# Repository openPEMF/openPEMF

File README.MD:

# <openPEMF>

## Description

Open source PEMF project that includes the hardware and firmware for anyone looking to build their own PEMF device

- Aren't there already some open source PEMF projects?  
    Yes, but many of them do not create the same fields used in the majority of published PEMF parameters. Most of them also have switching characteristics that cause spurious spike and oscillations that could be considered "dirty electricity"

- Why share this project?  
    Because PEMF with the right parameters has the ability to change peoples lives. From regenerating cartilage to reducing inflammation, many people get out of pain they have had for years. Something this powerful should not be stuck behind high price tags.

- What problem does it solve?  
    PEMF devices with good parameters cost a lot, cheap PEMF devices do not create magnetic fields that use the parameters used in the majority of PEMF studies

This open source PEMF project provides all the files necessary to make your own PEMF device that can be used to re-create the majority of PEMF parameters used in the majority of published PEMF studies.

PEMF has been proven to do lots of amazing things including regenerate cartilage and decrease inflammation, but don't take our word for it, go read some of the published studies and take a look at the science yourself!

The project allows you to tune your own magnetic field intensity and slew rate. This can be accomplished by either changing the voltage from the power supply, or by changing the pulse width.

Reach out with any questions or suggestions! Lets build this together and create a future where all people can access PEMF and benefit from the improved quality of life!
You can reach us at openpemf@gmail.com

## Table of Contents

- [How To Build](#How-to-build)
- [Usage](#usage)
- [Features](#features)

## How to build

The Gerber files, BOM and .POS files are already for purchase at JLCPCB.com. You should be able to upload these to JLCPCB and order complete (or mostly complete - depending on part availability) PCBs ready to run!

Once you have your PCBs, the first thing that you will want to do is upload the arduino code. The file "TEST.ino" is set up to run at 10hz and if you don't want to make any changes you can simply upload this file using the Arduino IDE. You will need to install the Raspberry Pi Pico board definitions since this design uses an RP2040 as it's processor. If you want to re-upload code, there are 2 holes in the pcb that you can bridge with a paperclip to get it into bootloader mode.

If you are not familiar with arduino or PCB ordering we can send out a kit. Email us at openpemf@gmail.com.

This board is designed to fit in this enclosure:
https://www.ebay.com/itm/266629727778?mkcid=16&mkevt=1&mkrid=711-127632-2357-0&ssspo=g7l9ZZJUQN-&sssrc=2047675&ssuid=7-kgmmceqts&widget_ver=artemis&media=COPY

You can see that we used a simple circular connector to get the PEMF power through the enclosure. Ideally a 4 pin connector would be used for larger coils/currents. A handheld drill is an okay option to add the holes. Another option would be something 3D printed or laser cut. Please contribute these if you end up making them!

The coil should be wound from some form of wire. The closer the wires are together, the more efficient the coil will be. Using regular insulated wire still works well, but you will get more magnetic field from using enameled magnet wire.

Here is what our prototype coil looked like:

This sensor is great to see what the fields look like around your coil. Simply give it power and connect it to an oscilloscope:
https://www.digikey.com/en/products/detail/asahi-kasei-microdevices-akm/EQ733L/5822654

The coil we made had around 3 mT at the center, and around 10 mT close to the wires.

You will want a power supply that can run the board well. We found that this one worked well:
https://www.digikey.com/en/products/detail/fsp-technology-inc/FSP040-DWAN3/15713237 

## Usage
Simply place the loop over any part of your body that needs improvement. We like to look up published studies to see how long to use the PEMF for. You can even wind coils that are smaller with higher intensity or larger for a larger magnetic field.

## Features

There are a lot of features to OpenPEMF! Here are a few:
* Mosfet gate slew is limited -  this prevents parasitic turn on during the falling side of the signal
* There is an RC snubber across the h-bridge, removing certain oscillations that are not wanted
* Bi-polar pulses
* Programmable frequencies

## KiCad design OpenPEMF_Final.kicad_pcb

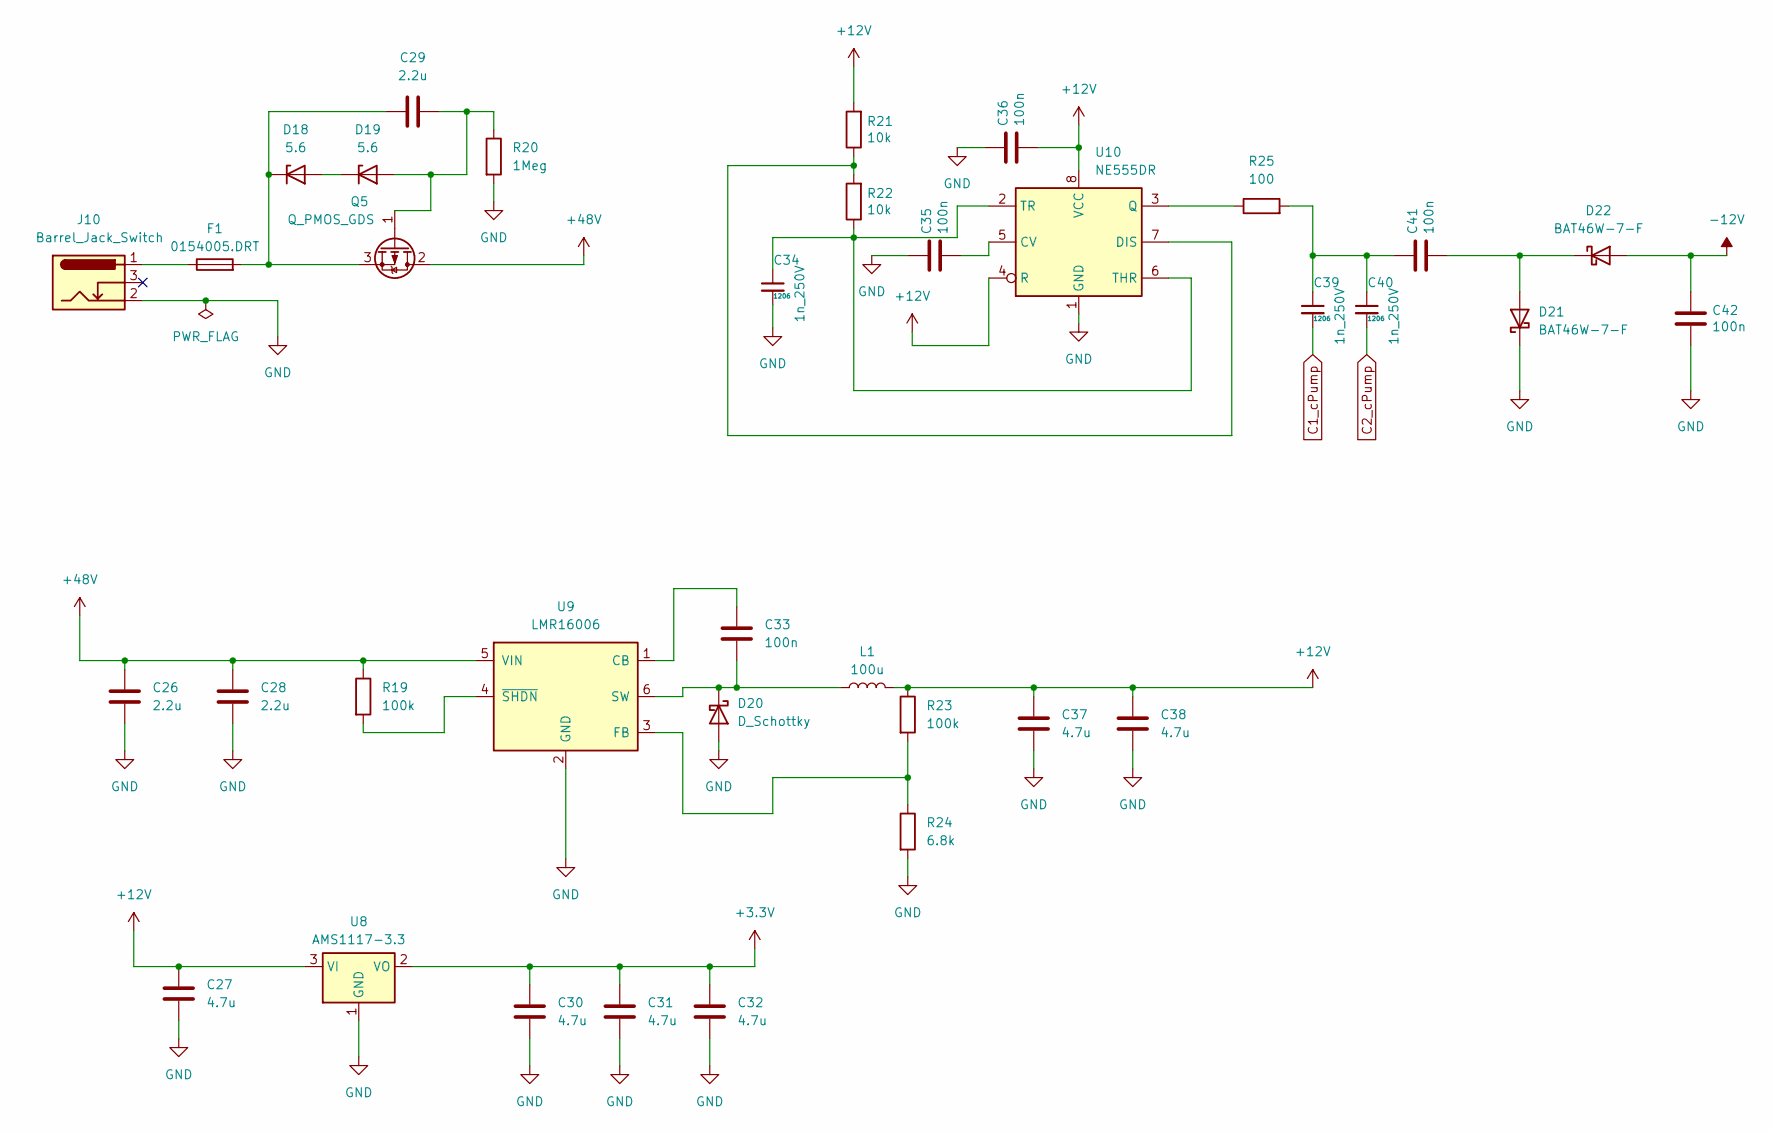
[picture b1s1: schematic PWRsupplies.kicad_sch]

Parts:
C26, C28, C29: 2.2u; C_1206_3216Metric
C27, C30, C31, C32, C37, C38: 4.7u; C_1206_3216Metric
C33: 100n; C_0805_2012Metric
C34, C39, C40: 1n_250V; C_1206_3216Metric
C35, C36, C41, C42: 100n; C_0402_1005Metric
D18, D19: 5.6; D_MiniMELF
D20: D_Schottky; D_SMA
D21, D22: BAT46W-7-F; D_SOD-123
F1: 0154005.DRT; Fuseholder_Littelfuse_Nano2_154x
J10: Barrel_Jack_Switch; C319099
L1: 100u; L_Coilcraft_XAL6060-XXX
Q5: Q_PMOS_GDS; TO-252-2
R19, R23: 100k; C_0603_1608Metric
R20: 1Meg; C_0603_1608Metric
R21, R22: 10k; R_0603_1608Metric
R24: 6.8k; R_0603_1608Metric
R25: 100; R_0402_1005Metric
U8: AMS1117-3.3; SOT-223-3_TabPin2
U9: LMR16006; SOT-23-6
U10: NE555DR; SOIC-8_3.9x4.9mm_P1.27mm

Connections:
+3.3V: C30.1, C31.1, C32.1, U8.2 (VO); also elsewhere on the board
+12V: C27.1, C36.2, C37.1, C38.1, L1.2, R21.2, R23.1, U8.3 (VI), U10.4 (R), U10.8 (VCC); also elsewhere on the board
+48V: C26.1, C28.1, Q5.2 (D), R19.1, U9.5 (VIN); also elsewhere on the board
-12V: C42.1, D22.2 (A); also elsewhere on the board
C1_cPump: C39.2; also elsewhere on the board
C2_cPump: C40.2; also elsewhere on the board
GND: C26.2, C27.2, C28.2, C30.2, C31.2, C32.2, C34.2, C35.1, C36.1, C37.2, C38.2, C42.2, D20.2 (A), D21.1 (K), J10.2, R20.2, R24.2, U8.1 (GND), U9.2 (GND), U10.1 (GND); also elsewhere on the board
unnamed: C39.1, C40.1, C41.1, R25.2
unnamed: D18.2 (A), D19.1 (K)
unnamed: C29.1, D18.1 (K), F1.2, Q5.3 (S)
unnamed: C29.2, D19.2 (A), Q5.1 (G), R20.1
unnamed: C33.2, D20.1 (K), L1.1, U9.6 (SW)
unnamed: C41.2, D21.2 (A), D22.1 (K)
unnamed: F1.1, J10.1
unnamed: C33.1, U9.1 (CB)
unnamed: R23.2, R24.1, U9.3 (FB)
unnamed: R19.2, U9.4 (~SHDN)
unnamed: C35.2, U10.5 (CV)
unnamed: R21.1, R22.2, U10.7 (DIS)
unnamed: R25.1, U10.3 (Q)
unnamed: C34.1, R22.1, U10.2 (TR), U10.6 (THR)

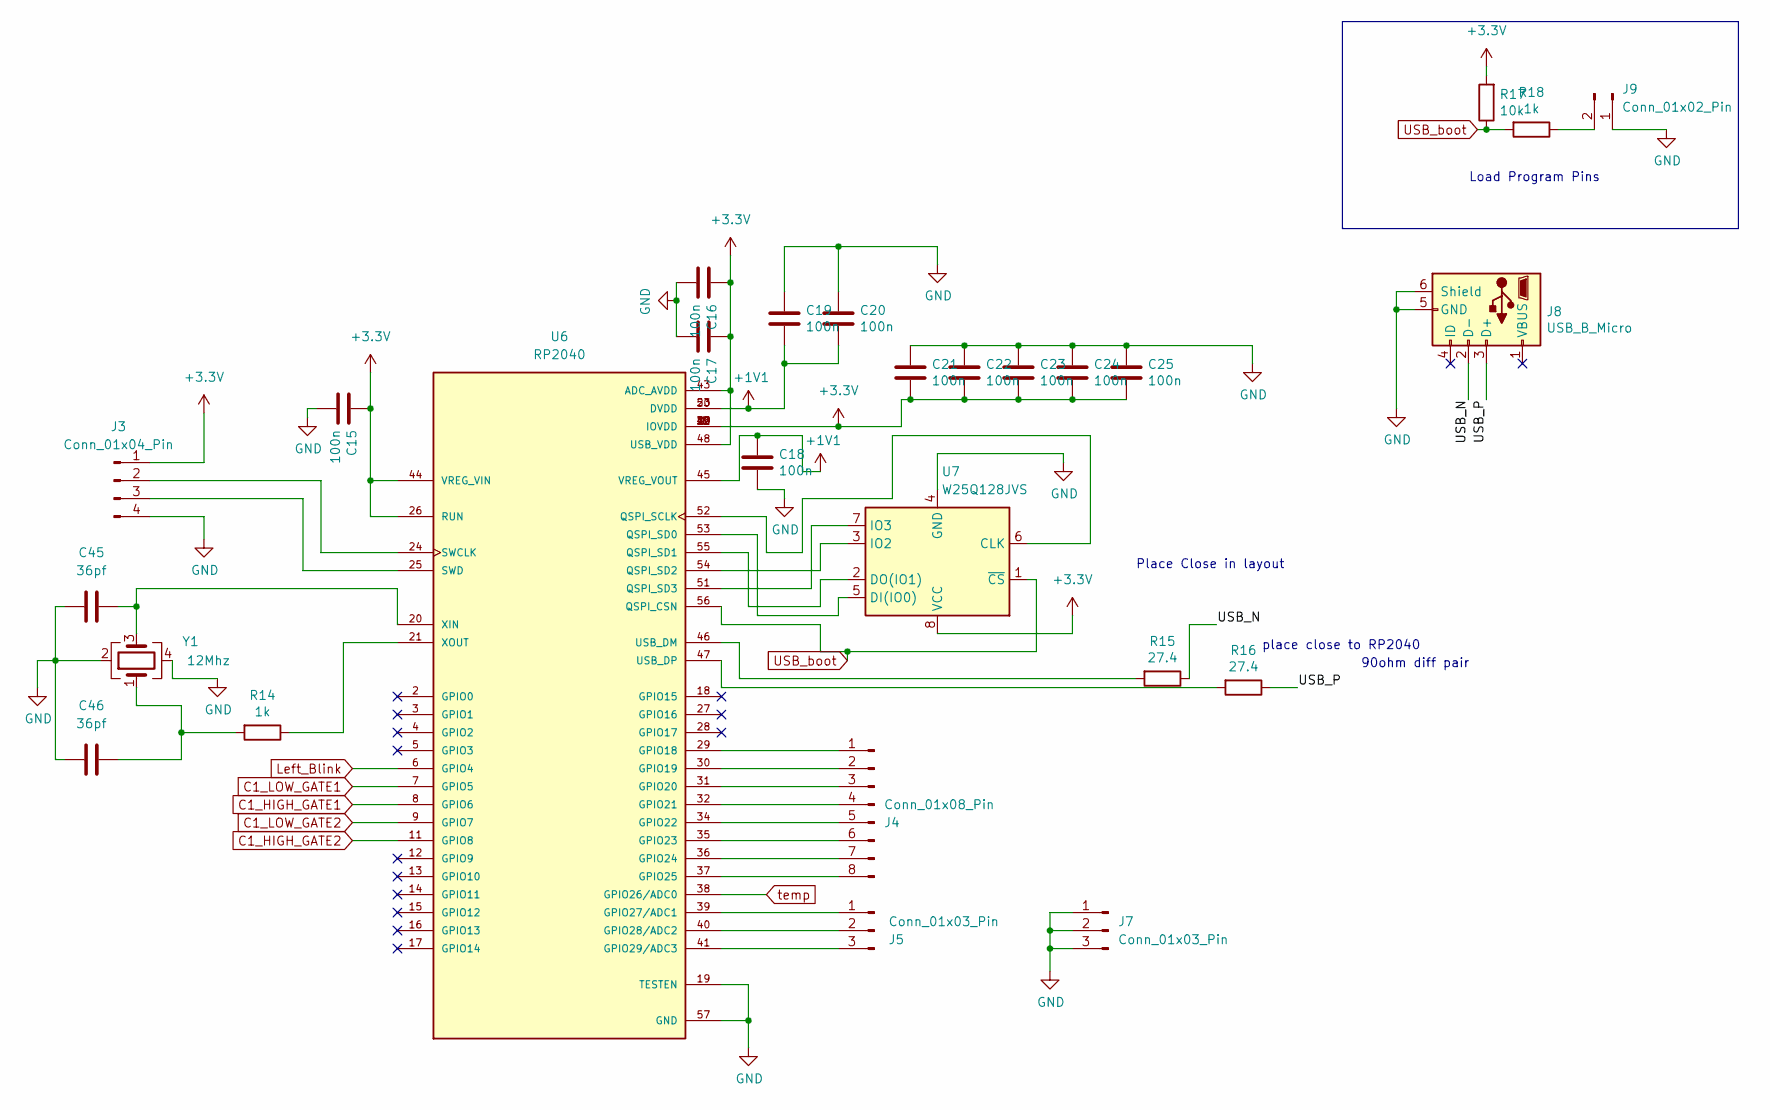
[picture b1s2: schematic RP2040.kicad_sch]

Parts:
C15, C16, C17, C18, C19, C20, C21, C22, C23, C24, C25: 100n; C_0402_1005Metric
C45, C46: 36pf; C_0402_1005Metric
J3: Conn_01x04_Pin; PinHeader_1x04_P1.00mm_Vertical
J4: Conn_01x08_Pin; PinHeader_1x08_P1.00mm_Vertical
J5, J7: Conn_01x03_Pin; PinHeader_1x03_P1.00mm_Vertical
J8: USB_B_Micro; AMPHENOL_10118194-0001LF
J9: Conn_01x02_Pin; PinHeader_1x02_P1.27mm_Vertical
R14, R18: 1k; R_0603_1608Metric
R15, R16: 27.4; R_0402_1005Metric
R17: 10k; R_0603_1608Metric
U6: RP2040; PARTREV 1.6.1
U7: W25Q128JVS; SOIC-8_5.23x5.23mm_P1.27mm
Y1: 12Mhz; Crystal_SMD_3225-4Pin_3.2x2.5mm

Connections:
+1V1: C18.1, C19.2, C20.2, U6.23 (DVDD), U6.45 (VREG_VOUT), U6.50 (DVDD)
+3.3V: C15.1, C16.1, C17.1, C21.2, C22.2, C23.2, C24.2, C25.2, J3.1, R17.2, U6.1 (IOVDD), U6.10 (IOVDD), U6.22 (IOVDD), U6.26 (RUN), U6.33 (IOVDD), U6.42 (IOVDD), U6.43 (ADC_AVDD), U6.44 (VREG_VIN), U6.48 (USB_VDD), U6.49 (IOVDD), U7.8 (VCC); also elsewhere on the board
/RP2040/USB_N: J8.2 (D-), R15.1
/RP2040/USB_P: J8.3 (D+), R16.1
C1_HIGH_GATE1: U6.8 (GPIO6); also elsewhere on the board
C1_HIGH_GATE2: U6.11 (GPIO8); also elsewhere on the board
C1_LOW_GATE1: U6.7 (GPIO5); also elsewhere on the board
C1_LOW_GATE2: U6.9 (GPIO7); also elsewhere on the board
GND: C15.2, C16.2, C17.2, C18.2, C19.1, C20.1, C21.1, C22.1, C23.1, C24.1, C25.1, C45.2, C46.2, J3.4, J7.1, J7.2, J7.3, J8.5 (GND), J8.6 (Shield), J9.1, U6.19 (TESTEN), U6.57 (GND), U7.4 (GND), Y1.2, Y1.4; also elsewhere on the board
Left_Blink: U6.6 (GPIO4)
unnamed: C46.1, R14.2, Y1.1
unnamed: J3.2, U6.24 (SWCLK)
unnamed: J3.3, U6.25 (SWD)
unnamed: J4.1, U6.29 (GPIO18)
unnamed: J4.2, U6.30 (GPIO19)
unnamed: J4.3, U6.31 (GPIO20)
unnamed: J4.4, U6.32 (GPIO21)
unnamed: J4.5, U6.34 (GPIO22)
unnamed: J4.6, U6.35 (GPIO23)
unnamed: J4.7, U6.36 (GPIO24)
unnamed: J4.8, U6.37 (GPIO25)
unnamed: J5.1, U6.39 (GPIO27/ADC1)
unnamed: J5.2, U6.40 (GPIO28/ADC2)
unnamed: J5.3, U6.41 (GPIO29/ADC3)
unnamed: J9.2, R18.1
unnamed: U6.52 (QSPI_SCLK), U7.6 (CLK)
unnamed: U6.53 (QSPI_SD0), U7.5 (DI(IO0))
unnamed: U6.55 (QSPI_SD1), U7.2 (DO(IO1))
unnamed: U6.54 (QSPI_SD2), U7.3 (IO2)
unnamed: U6.51 (QSPI_SD3), U7.7 (IO3)
unnamed: R15.2, U6.46 (USB_DM)
unnamed: R16.2, U6.47 (USB_DP)
unnamed: C45.1, U6.20 (XIN), Y1.3
unnamed: R14.1, U6.21 (XOUT)
USB_boot: R17.1, R18.2, U6.56 (QSPI_CSN), U7.1 (~CS)
temp: U6.38 (GPIO26/ADC0)

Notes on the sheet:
Load Program Pins
Place Close in layout
place close to RP2040
90ohm diff pair

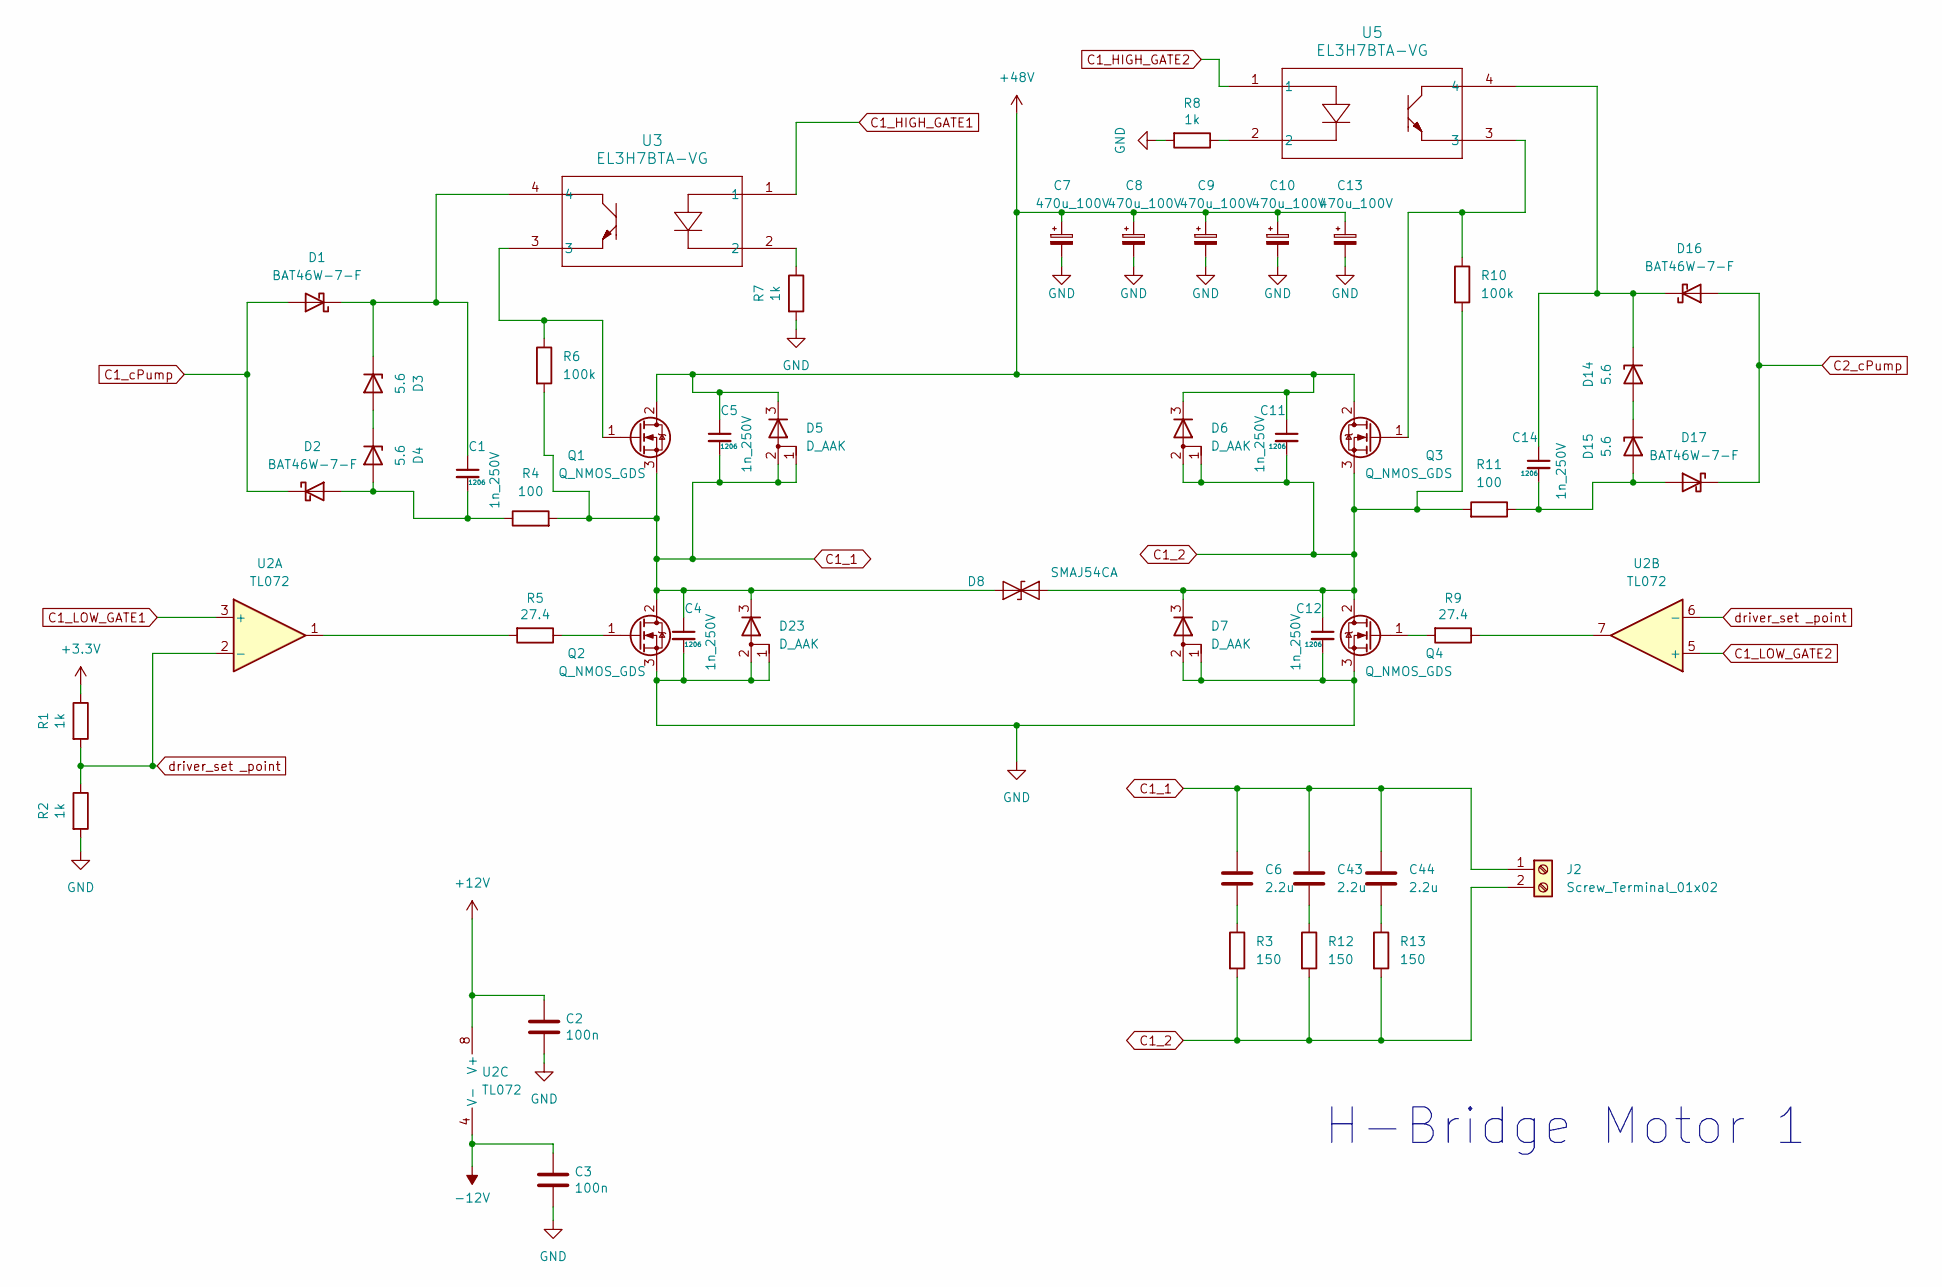
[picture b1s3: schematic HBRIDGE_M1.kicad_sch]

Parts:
C1, C4, C5, C11, C12, C14: 1n_250V; C_1206_3216Metric
C2, C3: 100n; C_0402_1005Metric
C6, C43, C44: 2.2u; C_1206_3216Metric
C7, C8, C9, C10, C13: 470u_100V; CP_Radial_D16.0mm_P7.50mm
D1, D2, D16, D17: BAT46W-7-F; D_SOD-123
D3, D4, D14, D15: 5.6; D_MiniMELF
D5, D6, D7, D23: D_AAK; TO-277A
D8: SMAJ54CA; D_SMA
J2: Screw_Terminal_01x02; TerminalBlock_Phoenix_MKDS-1,5-2-5.08_1x02_P5.08mm_Horizont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
Q1, Q2, Q3, Q4: Q_NMOS_GDS; TO-263-2
R1, R2, R7, R8: 1k; R_0603_1608Metric
R3, R12, R13: 150; R_0805_2012Metric
R4, R11: 100; R_0402_1005Metric
R5, R9: 27.4; R_0402_1005Metric
R6, R10: 100k; C_0603_1608Metric
U2: TL072; SOIC-8_3.9x4.9mm_P1.27mm
U3, U5: EL3H7BTA-VG; SOIC_BTA-VG_EVS

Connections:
+3.3V: R1.1; also elsewhere on the board
+12V: C2.1, U2.8 (V+); also elsewhere on the board
+48V: C5.1, C7.1, C8.1, C9.1, C10.1, C11.1, C13.1, D5.3 (K), D6.3 (K), Q1.2 (D), Q3.2 (D); also elsewhere on the board
-12V: C3.1, U2.4 (V-); also elsewhere on the board
C1_1: C4.1, C5.2, C6.1, C43.1, C44.1, D5.1 (A), D5.2 (A), D8.2 (A2), D23.3 (K), J2.1, Q1.3 (S), Q2.2 (D), R4.2, R6.2
C1_2: C11.2, C12.1, D6.1 (A), D6.2 (A), D7.3 (K), D8.1 (A1), J2.2, Q3.3 (S), Q4.2 (D), R3.2, R10.2, R11.2, R12.2, R13.2
C1_HIGH_GATE1: U3.1; also elsewhere on the board
C1_HIGH_GATE2: U5.1; also elsewhere on the board
C1_LOW_GATE1: U2.3 (+); also elsewhere on the board
C1_LOW_GATE2: U2.5 (+); also elsewhere on the board
C1_cPump: D1.2 (A), D2.1 (K); also elsewhere on the board
C2_cPump: D16.2 (A), D17.1 (K); also elsewhere on the board
GND: C2.2, C3.2, C4.2, C7.2, C8.2, C9.2, C10.2, C12.2, C13.2, D7.1 (A), D7.2 (A), D23.1 (A), D23.2 (A), Q2.3 (S), Q4.3 (S), R2.2, R7.2, R8.2; also elsewhere on the board
unnamed: C6.2, R3.1
unnamed: C43.2, R12.1
unnamed: C44.2, R13.1
unnamed: C1.1, D1.1 (K), D3.1 (K), U3.4
unnamed: C1.2, D2.2 (A), D4.2 (A), R4.1
unnamed: D3.2 (A), D4.1 (K)
unnamed: D14.2 (A), D15.1 (K)
unnamed: C14.1, D14.1 (K), D16.1 (K), U5.4
unnamed: C14.2, D15.2 (A), D17.2 (A), R11.1
unnamed: Q1.1 (G), R6.1, U3.3
unnamed: Q2.1 (G), R5.1
unnamed: Q3.1 (G), R10.1, U5.3
unnamed: Q4.1 (G), R9.2
unnamed: R5.2, U2.1
unnamed: R7.1, U3.2
unnamed: R8.1, U5.2
unnamed: R9.1, U2.7
driver_set _point: R1.2, R2.1, U2.2 (-), U2.6 (-)

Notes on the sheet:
H-Bridge Motor 1

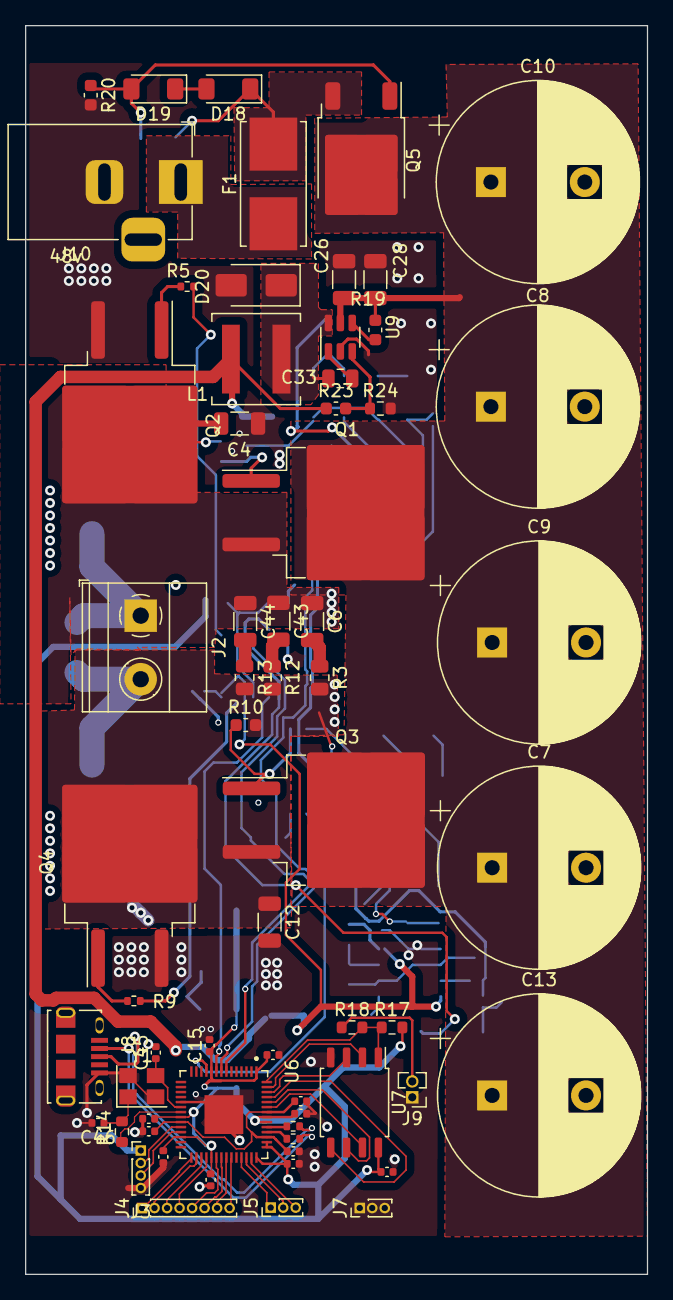
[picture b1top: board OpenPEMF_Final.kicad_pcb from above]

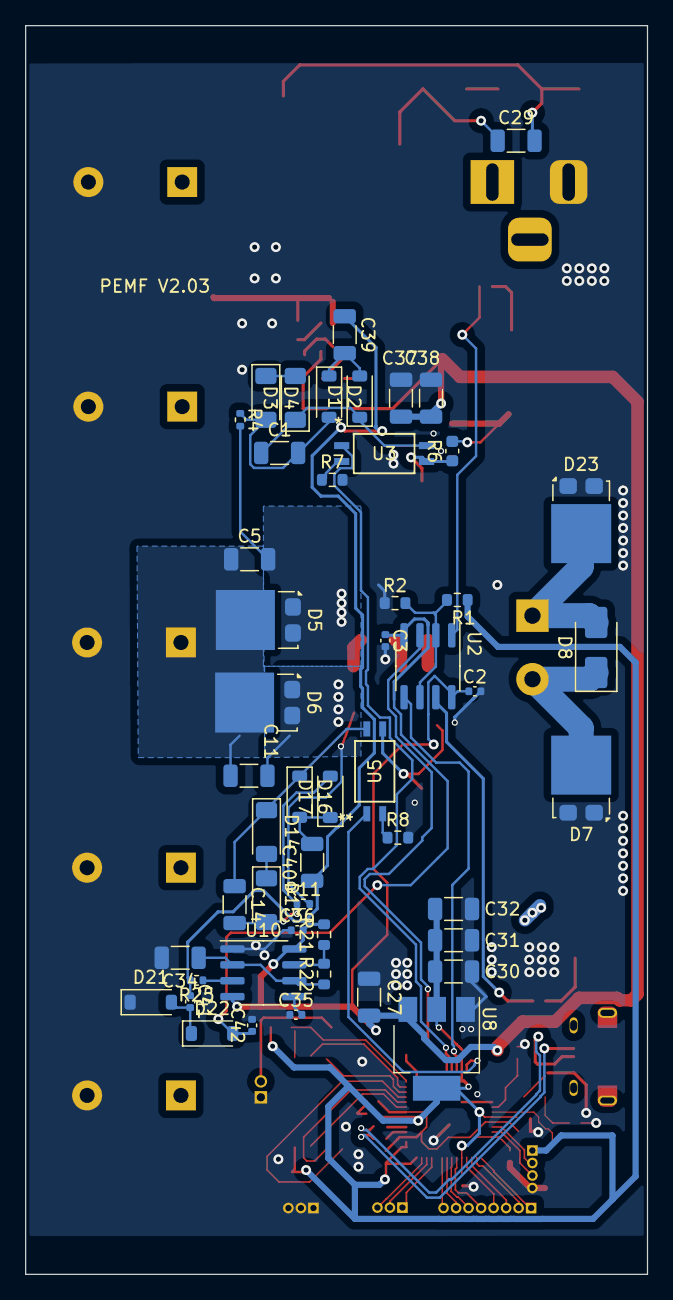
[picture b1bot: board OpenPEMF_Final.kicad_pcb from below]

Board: 4 copper layers, 49.7 x 99.8 mm, 113 parts (50 on the bottom side), 73 nets.

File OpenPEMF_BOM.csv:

"Reference","Value","Footprint","Field5"
"C1,C4,C5,C11,C12,C14,C34,C39,C40","1n_250V","Capacitor_SMD:C_1206_3216Metric","C915351"
"C2,C3,C15,C16,C17,C18,C19,C20,C21,C22,C23,C24,C25,C35,C36,C41,C42","100n","Capacitor_SMD:C_0402_1005Metric","C307331"
"C6,C26,C28,C29,C43,C44","2.2u","Capacitor_SMD:C_1206_3216Metric","C577211"
"C7,C8,C9,C10,C13","470u_100V","Capacitor_THT:CP_Radial_D16.0mm_P7.50mm","C340709"
"C27,C30,C31,C32,C37,C38","4.7u","Capacitor_SMD:C_1206_3216Metric","C29823"
"C33","100n","Capacitor_SMD:C_0805_2012Metric","C28233"
"C45,C46","36pf","Capacitor_SMD:C_0402_1005Metric","C541436"
"D1,D2,D16,D17,D21,D22","BAT46W-7-F","Diode_SMD:D_SOD-123","C83152"
"D3,D4,D14,D15,D18,D19","5.6","Diode_SMD:D_MiniMELF","C2982194"
"D5,D6,D7,D23","D_AAK","Package_TO_SOT_SMD:TO-277A","C2693410"
"D8","SMAJ54CA","Diode_SMD:D_SMA","C173507"
"D20","D_Schottky","Diode_SMD:D_SMA","C14996"
"F1","0154005.DRT","Fuse:Fuseholder_Littelfuse_Nano2_154x","C206917"
"J2","Screw_Terminal_01x02","TerminalBlock_Phoenix:TerminalBlock_Phoenix_MKDS-1,5-2-5.08_1x02_P5.08mm_Horizontal","C430601"
"J3,J4,J5,J7,J9","-- mixed values --","-- mixed values --",""
"J8","USB_B_Micro","OpenPEMFfp:AMPHENOL_10118194-0001LF","C132563"
"J10","Barrel_Jack_Switch","OpenPEMFfp:C319099","C720558"
"L1","100u","Inductor_SMD:L_Coilcraft_XAL6060-XXX","C341070"
"Q1,Q2,Q3,Q4","Q_NMOS_GDS","Package_TO_SOT_SMD:TO-263-2","C538034"
"Q5","Q_PMOS_GDS","Package_TO_SOT_SMD:TO-252-2","C2585"
"R1,R2,R7,R8,R14,R18","1k","Resistor_SMD:R_0603_1608Metric","C21190"
"R3,R12,R13","150","Resistor_SMD:R_0805_2012Metric","C17471"
"R4,R11,R25","100","Resistor_SMD:R_0402_1005Metric","C25076"
"R5,R9,R15,R16","27.4","Resistor_SMD:R_0402_1005Metric","C172043"
"R6,R10,R19,R23","100k","Capacitor_SMD:C_0603_1608Metric","C25803"
"R17,R21,R22","10k","Resistor_SMD:R_0603_1608Metric","C25804"
"R20","1Meg","Capacitor_SMD:C_0603_1608Metric","C22935"
"R24","6.8k","Resistor_SMD:R_0603_1608Metric","C23212"
"U2","TL072","Package_SO:SOIC-8_3.9x4.9mm_P1.27mm","C6961"
"U3,U5","EL3H7BTA-VG","OpenPEMFfp:SOIC_BTA-VG_EVS","C32565"
"U6","RP2040","OpenPEMFfp:RP2040","C2040"
"U7","W25Q128JVS","Package_SO:SOIC-8_5.23x5.23mm_P1.27mm","C97521"
"U8","AMS1117-3.3","Package_TO_SOT_SMD:SOT-223-3_TabPin2","C6186"
"U9","LMR16006","Package_TO_SOT_SMD:SOT-23-6","C87080"
"U10","NE555DR","Package_SO:SOIC-8_3.9x4.9mm_P1.27mm","C7593"
"Y1","12Mhz","Crystal:Crystal_SMD_3225-4Pin_3.2x2.5mm","C9002"

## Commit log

2024-12-11 added README
2024-12-11 added license
2024-12-13 added readme photos
2024-12-27 added photos
2024-12-27 added arduino program
